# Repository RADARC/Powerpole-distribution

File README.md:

# Powerpole-distribution
Anderson Powerpole distribution board with reverse polarity and over voltage protection.
Designed primarily for amateur radio use.

* 4 outputs rated at 30A with a combined 30A rating.
* TVS diodes to dissipate any transient voltage spikes.
* SCR based crowbar circuit for over voltage protection.
* Latching relay to disconnect supply if the crowbar cuircuit triggers as the input fuse may take time to blow depending on the available current from the supply.
* Diode protection around the relay and enable switch to stop the output from being enabled if the polarity is reversed.
* Input fuse for added protection.
* Output fuses to protect devices which may be rated at lower currents.

# Versions
V1.1 has the powerpole silkscreen updated to indicate the true outline of the socket. The pad and holes for sw1 have been enlarged.
# Current status
Final version of the PCB (V1.1) is complete.
Trip voltage is between 15.5V and 15.9V depending on how fast the input voltage seems to rise.
# Current and voltage meter
The circuit is designed to support the use of an ammeter in order to have a voltage and current display in the same case with the board.
A suitable meter would be https://www.aliexpress.com/item/33010218601.html. There are many sellers selling similar meters. I would suggest getting
at the very least a 50A rated one and ideally 100A as the voltage drop across the current shunt will be less.
Take note that the current shunt is wired between the netative of the input and outputs. If the power supply has a grounded negative connection then
return current can flow through ground instead of the negative causing an incorrect current reading. It is undesirable for this to happen anyway
so an incorrect current reading in this case is probably a good indication that there is something wrong anyway.
# Assembly tips
* When soldering the powerpole sockets asemble them and insert the pins and then solder to the PCB. The shells are fine with the high temperatures
during soldering. Also it helps to plug something into them when soldering the first contact to check that they are perfectly vertical. Otherwise it is not easy
to tell and you may not realise they are at an angle until something is plugged in.
* When soldering the relay, powerpole contacts and the fuse holders use plenty of heat and fine solder and try to get the solder to flow right through to the top surface.
Both surfaces are used for carrying the large currents so it's important to have a good contact between the pins and both surfaces and not rely on the small amount of
copper in the plated through hole to conduct both sides.
* The electrolytic capacitor (C3) is a bit too tall as it would require the top of the case to be quite high making removing the fuses difficult or a hole put in the lid
for the capacitor to poke though. Therefore either lie it down or just solder it to the reverse of the board as there is plenty of space under the PCB as the height
of the case is governed by the ampmeter and the cables which plug in underneath.
* A 50W soldering iron was fine for soldering all the contacts even onto the large ground planes. The only joint which was problematic was the relay contact furthest away
from the input fuse which is probably connected to the armature and sucked away a lot of the heat.
# 3D case
A case has been designed for the PCB and the current shunt and meter mentioned above.
I have made the designs public in Tinkercad so people can modify it to fit different meters or remove the option if desired.
All screws are M3 and I made made use of metal threaded inserts.  
Base - https://www.tinkercad.com/things/e5ViJ67TmCy  
Top - https://www.tinkercad.com/things/gQ1BUrXmc8q

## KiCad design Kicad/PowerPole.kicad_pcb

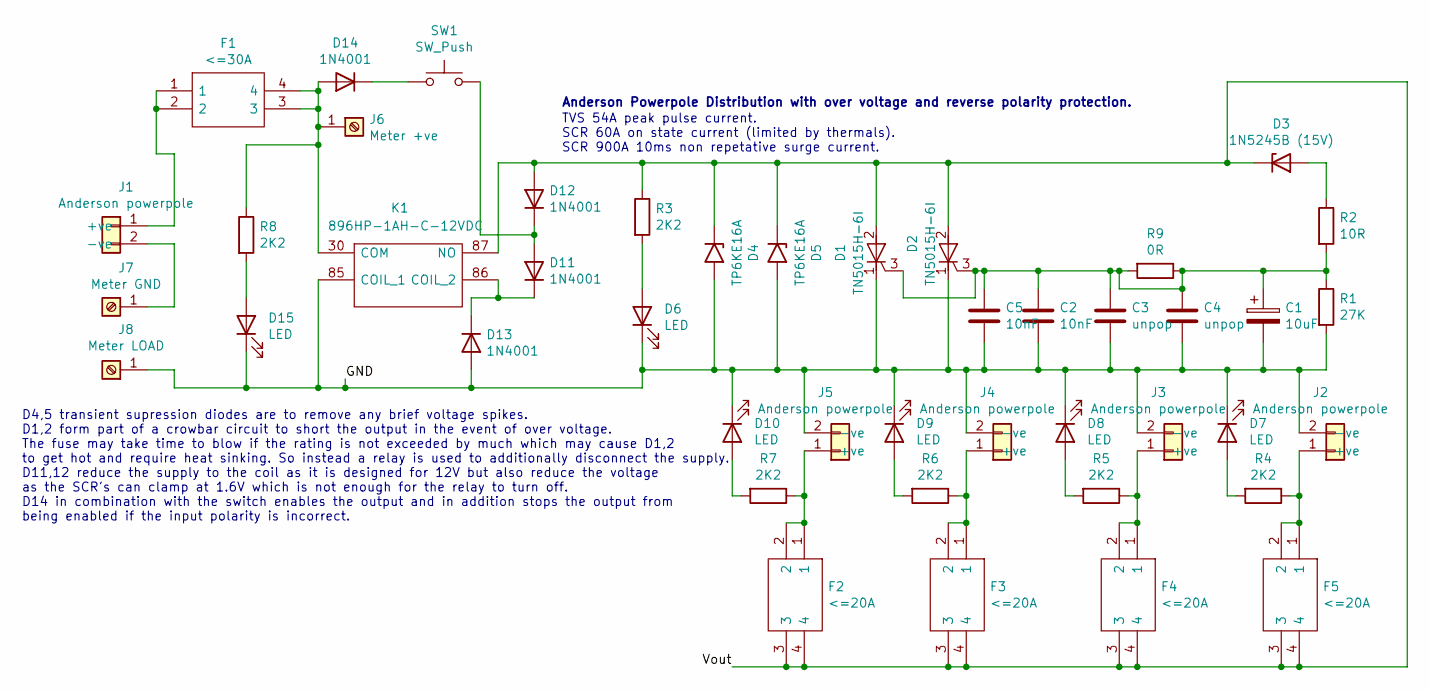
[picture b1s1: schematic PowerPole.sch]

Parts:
C1: 10uF; CP_Radial_D5.0mm_P2.00mm
C2, C5: 10nF; C_Rect_L7.0mm_W4.5mm_P5.00mm
C3, C4: unpop; C_Rect_L7.0mm_W4.5mm_P5.00mm
D1, D2: TN5015H-6I; TO-220-3_Horizontal_TabDown
D3: 1N5245B (15V); D_A-405_P7.62mm_Horizontal
D4, D5: TP6KE16A; D_DO-201AE_P15.24mm_Horizontal
D6, D7, D8, D9, D10, D15: LED; LED_D5.0mm
D11, D12, D13, D14: 1N4001; D_DO-34_SOD68_P7.62mm_Horizontal
F1: <=30A; 355720; Mouser Part Number 534-3557-20
F2, F3, F4, F5: <=20A; 355720; Mouser Part Number 534-3557-20
J1, J2, J3, J4, J5: Anderson powerpole; Anderson_powerpole_2w
J6: Meter +ve; SolderWire-0.5sqmm_1x01_D0.9mm_OD2.1mm
J7: Meter GND; SolderWire-2.5sqmm_1x01_D2.4mm_OD4.4mm
J8: Meter LOAD; SolderWire-2.5sqmm_1x01_D2.4mm_OD4.4mm
K1: 896HP-1AH-C-12VDC; 896HP1AHC12VDC; Mouser Part Number 893-896HP1AHC12VDC
R1: 27K; R_Axial_DIN0207_L6.3mm_D2.5mm_P10.16mm_Horizontal
R2: 10R; R_Axial_DIN0207_L6.3mm_D2.5mm_P10.16mm_Horizontal
R3, R4, R5, R6, R7, R8: 2K2; R_Axial_DIN0207_L6.3mm_D2.5mm_P10.16mm_Horizontal
R9: 0R; R_Axial_DIN0207_L6.3mm_D2.5mm_P10.16mm_Horizontal
SW1: SW_Push; SolderWire-0.25sqmm_1x02_P4.2mm_D0.65mm_OD1.7mm

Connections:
/GND: C1.2, C2.2, C3.2, C4.2, C5.2, D1.1 (K), D2.1 (K), D4.2 (A2), D5.2 (A2), D6.1 (K), D7.1 (K), D8.1 (K), D9.1 (K), D10.1 (K), D13.2 (A), D15.1 (K), J2.2 (-ve), J3.2 (-ve), J4.2 (-ve), J5.2 (-ve), J8.1, K1.85 (COIL_1), R1.2
/Vout: D1.2 (A), D2.2 (A), D3.1 (K), D4.1 (A1), D5.1 (A1), D12.2 (A), F2.3, F2.4, F3.3, F3.4, F4.3, F4.4, F5.3, F5.4, K1.87 (NO), R3.1
unnamed: C1.1, C2.1, C3.1, C4.1, C5.1, D1.3 (G), D2.3 (G), R1.1, R2.2, R9.1, R9.2
unnamed: D3.2 (A), R2.1
unnamed: D6.2 (A), R3.2
unnamed: D7.2 (A), R4.2
unnamed: D8.2 (A), R5.2
unnamed: D9.2 (A), R6.2
unnamed: D10.2 (A), R7.2
unnamed: D11.1 (K), D13.1 (K), K1.86 (COIL_2)
unnamed: D11.2 (A), D12.1 (K), SW1.2
unnamed: D14.1 (K), SW1.1
unnamed: D14.2 (A), F1.3, F1.4, J6.1, K1.30 (COM), R8.1
unnamed: D15.2 (A), R8.2
unnamed: F1.1, F1.2, J1.1 (+ve)
unnamed: F2.1, F2.2, J5.1 (+ve), R7.1
unnamed: F3.1, F3.2, J4.1 (+ve), R6.1
unnamed: F4.1, F4.2, J3.1 (+ve), R5.1
unnamed: F5.1, F5.2, J2.1 (+ve), R4.1
unnamed: J1.2 (-ve), J7.1

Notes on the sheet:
Anderson Powerpole Distribution with over voltage and reverse polarity protection.
D4,5 transient supression diodes are to remove any brief voltage spikes. D1,2 form part of a crowbar circuit to short the output in the event of over voltage. The fuse may take time to blow if the rating is not exceeded by much which may cause D1,2 to get hot and require heat sinking. So instead a 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
TVS 54A peak pulse current. SCR 60A on state current (limited by thermals). SCR 900A 10ms non repetative surge current.

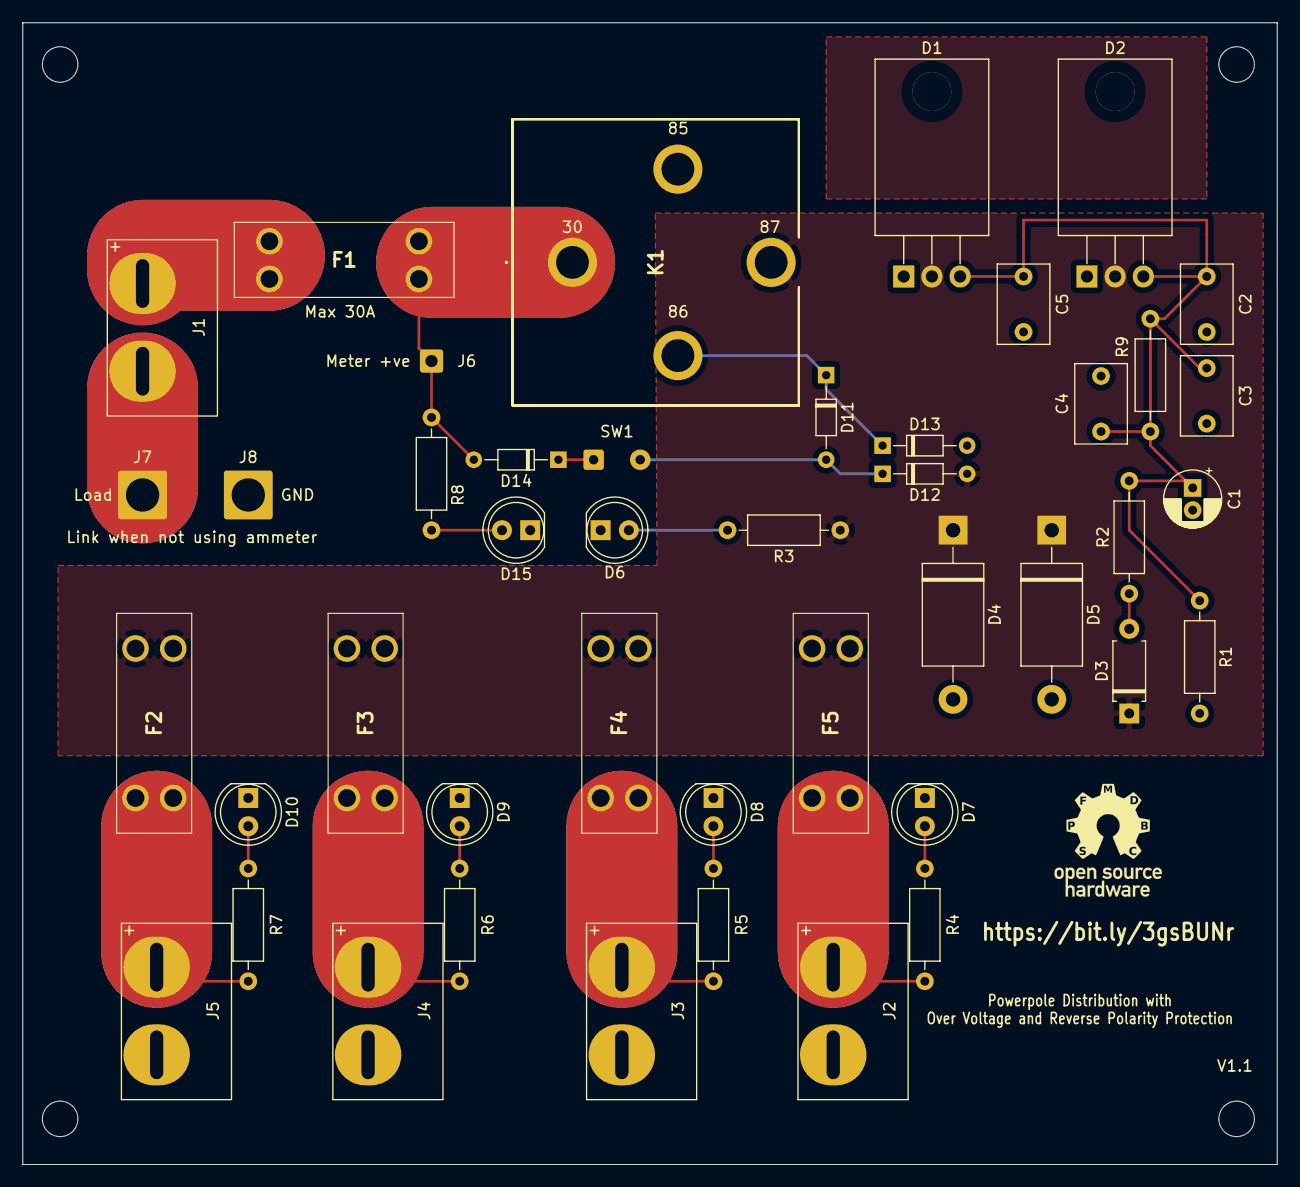
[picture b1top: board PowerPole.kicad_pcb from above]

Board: 2 copper layers, 113.0 x 102.9 mm, 48 parts (0 on the bottom side), 20 nets.

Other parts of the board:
 : MountingHole_3.2mm_M3
 #2,  #3,  #4: MountingHole_3.2mm_M3

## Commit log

2021-04-17 Updated powerpole pcb footprint
2021-04-17 Added connections for power and voltage meter
2021-04-18 PCB update
2021-04-18 renamed pcb images
2021-04-19 Fixed value of led resistors
2021-04-19 PCB silkscreen update
2021-04-19 Added open source logo to pcb
2021-04-24 Added mounting holes
2021-04-24 Updated gerbers
2021-04-25 Updated pcb bitmaps
2021-05-13 Updated to v1.1. powerpole sinkscreen and sw1 pads updated
2021-09-08 3D case design
2021-09-09 Update case deign
2024-09-25 Update PowerPole Case Base.stl
    2mm wider supports to accept thicker metal threaded inserts
